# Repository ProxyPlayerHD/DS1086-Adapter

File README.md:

# DS1086-Adapter
SMT to DIP-8 Adapter for the DS1086 Programmable Clock Generator, Including an Arduino Sketch to program the chip

This repo has the full Kicad Project including gerbers, and a PDF of the schematic. Of course it also includes the Arduino Sketch which contains the code nessesary to program the chip over a CLI like interface via serial.

It's fairly simple:

first make sure that whatever terminal you use for the Arduino uses LF characters for new lines (no CR or CR+LF)  
then connect the 4 pins of the Adapter (5V, GND, SDA, SCL) to the appropriate pins on whatever 5V arduino board you're using  
finally power the thing up and wait for the small splash screen  
after that you simply enter commands like with any other CLI, the supported commands are as follows:  

* help - displays a list of all commands and what they do
* get - displays the current clock speed of the DS1086
* set <freq. in kHz> - sets the clock speed of the DS1086 to the specified value
* write - saves the current clock speed to the EEPROM

note that the DAC Register always reads the same value regardless of the contents of the Register, so the read out can be off by up to 5MHz. if you want to be sure the speed is correct just use an Oscilloscope.

On a different note the headers for the programming interface are split because of space constraints as i wanted the whole thing to fit into the footprint of an actual DIP-8 Oscillator can.
If vertial space is a premium, the programming headers can be left unpopulated in which case you just put some wires into the holes and hold them with your fingers while programming it.

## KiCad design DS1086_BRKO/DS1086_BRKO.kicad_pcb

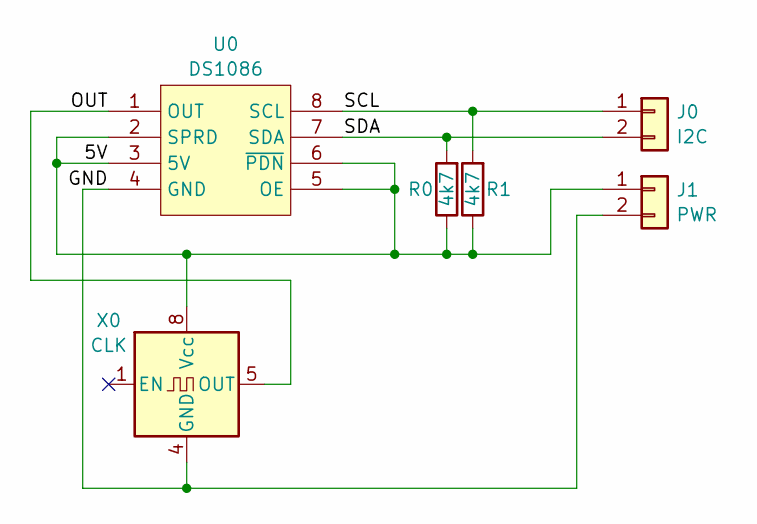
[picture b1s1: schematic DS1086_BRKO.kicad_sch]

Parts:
J0: I2C; PinHeader_1x02_P2.54mm_Vertical
J1: PWR; PinHeader_1x02_P2.54mm_Vertical
R0, R1: 4k7; R_Axial_DIN0204_L3.6mm_D1.6mm_P7.62mm_Horizontal
U0: DS1086; MSOP-8_3x3mm_P0.65mm
X0: CLK; Oscillator_DIP-8

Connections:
/5V: J1.1, R0.1, R1.1, U0.2 (SPRD), U0.3 (5V), U0.5 (OE), U0.6 (~PDN), X0.8 (Vcc)
/GND: J1.2, U0.4 (GND), X0.4 (GND)
/OUT: U0.1 (OUT), X0.5 (OUT)
/SCL: J0.1, R1.2, U0.8 (SCL)
/SDA: J0.2, R0.2, U0.7 (SDA)

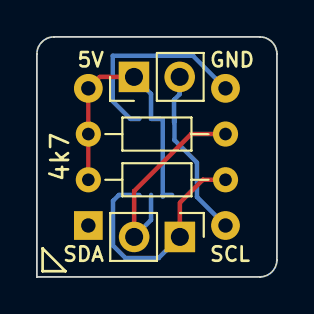
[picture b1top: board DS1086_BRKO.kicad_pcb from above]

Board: 2 copper layers, 13.3 x 13.3 mm, 6 parts (1 on the bottom side), 5 nets.
